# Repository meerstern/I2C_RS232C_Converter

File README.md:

# I2C_RS232C_Converter
I2C-RS232C Converter with Grove Connector

## 概要 
  * マイコンのI2CポートをRS232C通信ポートに変換するアダプタです
  * マイコンからI2Cデバイスとして制御し、UARTのボーレート設定、送信、受信処理をすることができます
  * I2C/UARTプロトコルブリッジ[SC16IS750][1]とRS232C変換IC ADM3202を搭載しています
  * I2CはGrove互換コネクタとなっており、3.3V/5V電源に対応しています
  * RS232CポートはD-sub9ピンのオスコネクタを搭載しています
  * I2C/UARTプロトコルブリッジSC16IS750は64bytesのバッファを内蔵しています
  * 7.3728MHzの水晶発振子を搭載しており、マイコンのメインクロックから独立してUARTのボーレート設定ができます  
  * デフォルトI2Cアドレスは8bit:0x9A(7bit:0x4D)です  

## 注意 
  * RS232Cレベル変換している信号はD-sub9ピンの受信の2ピン、送信の3ピンのみです  
  * D-sub9ピンの受信の2ピン、送信の3ピン、GNDの5ピン以外はTTLレベルのため、必要に応じて未接続にしてください(v1.0/v1.1のみ)
  * D-sub9ピンの受信の2ピン、送信の3ピン、GNDの5ピン以外のRTS/CDSはRS232Cレベルに変換されています(v1.2以降, v1.3はR14を必要に応じて実装してください)    
  * Arduino Uno以外の場合はサンプルコード内SC16IS750.cppの29行目付近のWire定義を必要に応じて変更してください  

## 販売サイト
  * [スイッチサイエンス][2]

[1]: https://www.nxp.com/products/peripherals-and-logic/signal-chain/bridges/single-uart-with-i2c-bus-spi-interface-64-bytes-of-transmit-and-receive-fifos-irda-sir-built-in-support:SC16IS740_750_760 "*1"

[2]: https://www.switch-science.com/products/6026

MIT Lisense

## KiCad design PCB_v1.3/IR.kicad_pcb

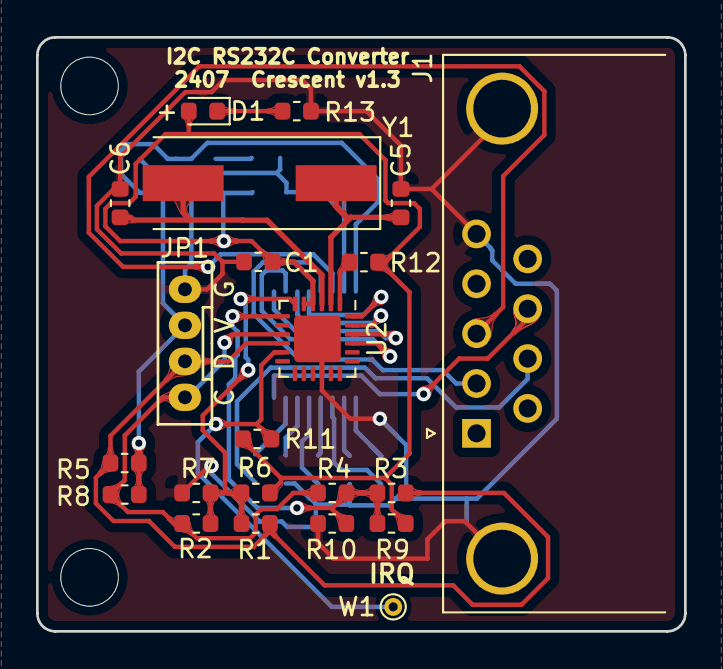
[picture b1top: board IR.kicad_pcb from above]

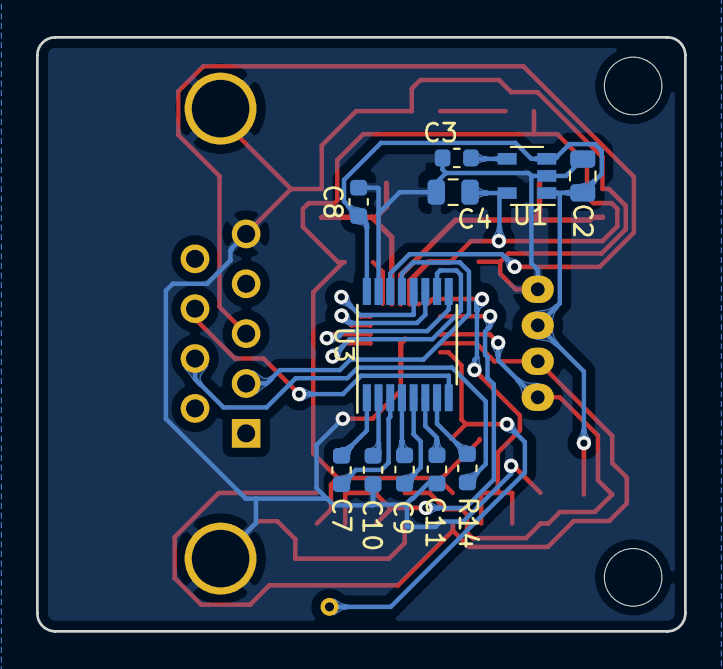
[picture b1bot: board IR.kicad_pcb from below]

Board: 2 copper layers, 36.0 x 33.0 mm, 35 parts (11 on the bottom side), 28 nets.

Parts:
C1, C7, C8, C9, C10, C11: 0.1u; C_0603_1608Metric
C2, C4: 10u; C_0805_2012Metric
C3: 0.01u; C_0603_1608Metric
C5, C6: 10p; C_0603_1608Metric
D1: LED; D_0603_1608Metric
J1: DSUB9; DSUB-9_Male_Horizontal_P2.77x2.84mm_EdgePinOffset7.70mm_Hou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
JP1: PINHD-1X4; GROVE
R1, R2, R3, R4, R6, R7, R9, R10, R14: 0; R_0603_1608Metric
R5, R8, R12: 4.7k; R_0603_1608Metric
R11, R13: 1k; R_0603_1608Metric
REF1, REF2: MountingHole_3.2mm_M3
U1: LD3985M33R_SOT23; SOT-23-5
U2: SC16IS750IBS; QFN-24-1EP_4x4mm_P0.5mm_EP2.6x2.6mm
U3: ADM232A; TSSOP-16_4.4x5mm_P0.65mm
W1: IRQ; TestPoint_THTPad_D1.0mm_Drill0.5mm
Y1: Crystal; Crystal_SMD_HC49-SD

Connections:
/3.3V: C1.1, C4.1, D1.2, R6.1, R9.1, R11.1, R12.1, U1.5, U2.4, U2.5
/5V: C2.1, C8.1, JP1.3, R5.1, R8.1, U1.1, U1.3, U3.16
/A0: R1.2, R2.2, R6.2, R7.2, U2.6
/A1: R3.2, R4.2, R9.2, R10.2, U2.7
/CTS: U2.22, U3.9
/CTSD: J1.8, U3.8
/IRQ: R11.2, U2.11, W1.1
/RST: R12.2, U2.1
/RTS: U2.21, U3.10
/RTSD: J1.7, R14.1
/RX: U2.24, U3.12
/RXD: J1.2, U3.13
/SCL: JP1.1, R2.1, R4.1, R8.2, U2.9
/SDA: JP1.2, R1.1, R3.1, R5.2, U2.10
/TX: U2.23, U3.11
/TXD: J1.3, U3.14
/XTAL1: C5.1, U2.2, Y1.1
/XTAL2: C6.1, U2.3, Y1.2
GND: C1.2, C2.2, C3.2, C4.2, C5.2, C6.2, C8.2, C10.1, C11.1, J1.0, J1.5, JP1.4, R7.1, R10.1, R13.2, U1.2, U2.16, U2.25, U3.15
unnamed: C3.1, U1.4
unnamed: C7.1, U3.1
unnamed: C7.2, U3.3
unnamed: C9.1, U3.4
unnamed: C9.2, U3.5
unnamed: C10.2, U3.2
unnamed: C11.2, U3.6
unnamed: D1.1, R13.1
unnamed: R14.2, U3.7

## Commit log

2019-11-09 Upload data
2019-11-09 Add Sample Code
2019-12-10 Add images
2024-07-03 Add V1.3
2024-07-03 Fix Figures
